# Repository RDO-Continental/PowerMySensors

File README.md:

# PowerMySensors
Code de notre module de mesure de puissance (Arduino + NRF + MySensors)

Mesure de puissance club RDO : MPRDO V1.0
 * Alimenté par un transfo qui sert aussi à la mesure de la puissance reelle.
 * Transmission par module NRF24L01 et protocole Mysensors
 * Basé sur le projet "openenergymonitor.org"

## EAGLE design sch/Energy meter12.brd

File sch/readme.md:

Schema de notre cartre de mesure

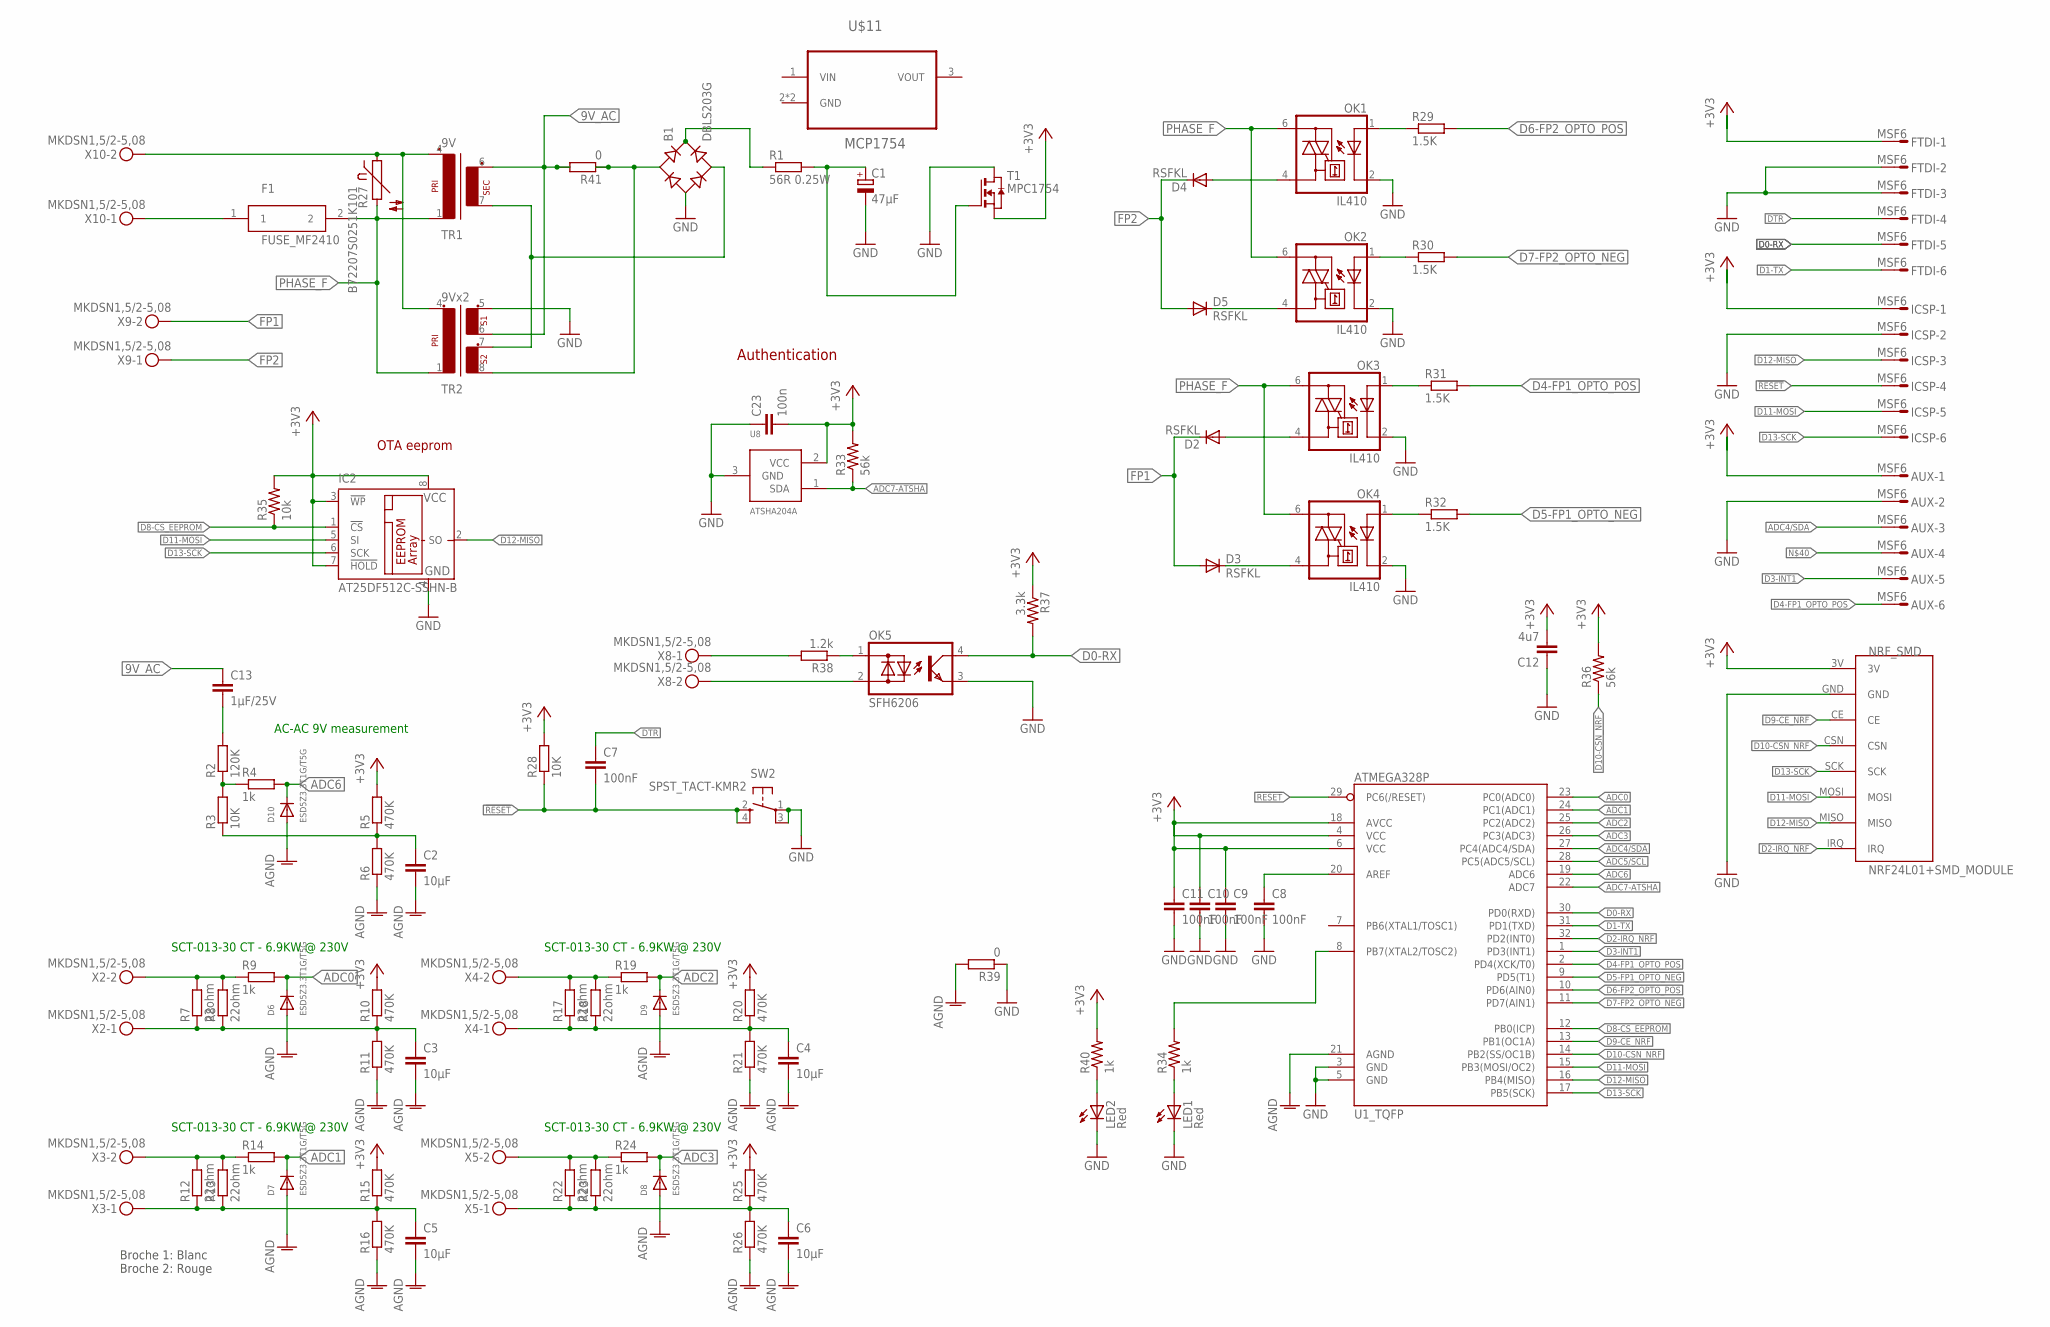
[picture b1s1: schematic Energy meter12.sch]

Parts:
AUX: MSF6
B1: DBLS203G; DBS
C1: 47µF; PANASONIC_D
C2, C3, C4, C5, C6: 10µF; C0805
C7, C8, C9, C10, C11: 100nF; C0603
C12: 4u7; 0805-CAP
C13: 1µF/25V; C0805
C23: 100n; 0603-CAP
D2, D3, D4, D5: RSFKL; SOD123
D6, D7, D8, D9, D10: ESD5Z3.3T1G/T5G; SOD-523
F1: FUSE_MF2410; 2410
FTDI: MSF6
IC2: AT25DF512C-SSHN-B; SO-08
ICSP: MSF6
LED1, LED2: Red; LED3MM
NRF_SMD: NRF24L01+SMD_MODULE
OK1, OK2, OK3, OK4: IL410; DIL06
OK5: SFH6206; DIL4-SMD
R1: 56R 0.25W; R1206
R2: 120K; R0603
R3, R28: 10K; R0603
R4, R9, R14, R19, R24: 1k; R0603
R5, R6, R10, R11, R15, R16, R20, R21, R25, R26: 470K; R0603
R7, R12, R17, R22: 22ohm; R1206
R8, R13, R18, R23: 22ohm; 0204/7
R27: B72207S0251K101; 07S0251
R29, R30, R31, R32: 1.5K; R0603
R33: 56k; 0603-RES
R34, R40: 1k; 0805-RES
R35: 10k; 0805-RES
R36: 56k; 0805-RES
R37: 3.3k; 0603-RES
R38: 1.2k; 0204/7
R39, R41: 0; R0603
SW2: SPST_TACT-KMR2; KMR2
T1: MPC1754; SOT89
TR1: 9V; PT150901
TR2: 9Vx2; EE20-2
U1_TQFP: ATMEGA328P; TQFP32-08
U8: ATSHA204A; SOT23
U$11: MCP1754; SOT89
X2, X3, X4, X5, X8, X9, X10: MKDSN1,5/2-5,08

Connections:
9V_AC: C13.1, R41.2, TR1.6 (S3), TR2.6 (4)
!RESET: C7.2, ICSP.4, R28.1, SW2.2 (S), SW2.4 (S1), U1_TQFP.29 (PC6(/RESET))
+3V3: AUX.1, C9.1, C10.1, C11.1, C12.2, C23.2, FTDI.1, IC2.3 (!WP), IC2.7 (!HOLD), IC2.8 (VCC), ICSP.1, NRF_SMD.3V, R5.2, R10.2, R15.2, R20.2, R25.2, R28.2, R33.2, R35.2, R36.2, R37.1, R40.2, T1.3 (S), U1_TQFP.4 (VCC), U1_TQFP.6 (VCC), U1_TQFP.18 (AVCC), U8.2 (VCC)
ADC0: D6.K (C), R9.2, U1_TQFP.23 (PC0(ADC0))
ADC1: D7.K (C), R14.2, U1_TQFP.24 (PC1(ADC1))
ADC2: D9.K (C), R19.2, U1_TQFP.25 (PC2(ADC2))
ADC3: D8.K (C), R24.2, U1_TQFP.26 (PC3(ADC3))
ADC4/SDA: AUX.3, U1_TQFP.27 (PC4(ADC4/SDA))
ADC5/SCL: U1_TQFP.28 (PC5(ADC5/SCL))
ADC6: D10.K (C), R4.2, U1_TQFP.19 (ADC6)
ADC7-ATSHA: R33.1, U1_TQFP.22 (ADC7), U8.1 (SDA)
AGND: C2.2, C3.2, C4.2, C5.2, C6.2, D6.A, D7.A, D8.A, D9.A, D10.A, R6.1, R11.1, R16.1, R21.1, R26.1, R39.2, U1_TQFP.21 (AGND)
D0-RX: FTDI.5, OK5.4 (C), R37.2, U1_TQFP.30 (PD0(RXD))
D1-TX: FTDI.6, U1_TQFP.31 (PD1(TXD))
D2-IRQ_NRF: NRF_SMD.IRQ, U1_TQFP.32 (PD2(INT0))
D3-INT1: AUX.5, U1_TQFP.1 (PD3(INT1))
D4-FP1_OPTO_POS: AUX.6, R31.2, U1_TQFP.2 (PD4(XCK/T0))
D5-FP1_OPTO_NEG: R32.2, U1_TQFP.9 (PD5(T1))
D6-FP2_OPTO_POS: R29.2, U1_TQFP.10 (PD6(AIN0))
D7-FP2_OPTO_NEG: R30.2, U1_TQFP.11 (PD7(AIN1))
D8-CS_EEPROM: IC2.1 (!CS), R35.1, U1_TQFP.12 (PB0(ICP))
D9-CE_NRF: NRF_SMD.CE, U1_TQFP.13 (PB1(OC1A))
D10-CSN_NRF: NRF_SMD.CSN, R36.1, U1_TQFP.14 (PB2(SS/OC1B))
D11-MOSI: IC2.5 (SI), ICSP.5, NRF_SMD.MOSI, U1_TQFP.15 (PB3(MOSI/OC2))
D12-MISO: IC2.2 (SO), ICSP.3, NRF_SMD.MISO, U1_TQFP.16 (PB4(MISO))
D13-SCK: IC2.6 (SCK), ICSP.6, NRF_SMD.SCK, U1_TQFP.17 (PB5(SCK))
DTR: C7.1, FTDI.4
FP1: D2.C, D3.A, X9.2
FP2: D4.C, D5.A, X9.1
GND: AUX.2, B1.-, C1.-, C8.2, C9.2, C10.2, C11.2, C12.1, C23.1, FTDI.2, FTDI.3, IC2.4 (GND), ICSP.2, LED1.K (C), LED2.K (C), NRF_SMD.GND, OK1.2 (C), OK2.2 (C), OK3.2 (C), OK4.2 (C), OK5.3 (E), R39.1, SW2.1, SW2.3 (P1), T1.2 (D), T1.2@1 (D), TR2.5 (3), U1_TQFP.3 (GND), U1_TQFP.5 (GND), U8.3 (GND)
unnamed: B1.AC1, R41.1, TR2.8 (6)
unnamed: C1.+, R1.2, T1.1 (G)
unnamed: R2.1, R3.2, R4.1
unnamed: C2.1, R3.1, R5.1, R6.2
unnamed: D4.A, OK1.4 (A1)
unnamed: R7.2, R8.2, R9.1, X2.2
unnamed: C3.1, R7.1, R8.1, R10.1, R11.2, X2.1
unnamed: LED2.A, R40.1
unnamed: R12.2, R13.2, R14.1, X3.2
unnamed: C5.1, R12.1, R13.1, R15.1, R16.2, X3.1
unnamed: R17.2, R18.2, R19.1, X4.2
unnamed: C4.1, R17.1, R18.1, R20.1, R21.2, X4.1
unnamed: R22.2, R23.2, R24.1, X5.2
unnamed: C6.1, R22.1, R23.1, R25.1, R26.2, X5.1
unnamed: C8.1, U1_TQFP.20 (AREF)
unnamed: D2.A, OK3.4 (A1)
unnamed: D5.C, OK2.4 (A1)
unnamed: OK1.1 (A), R29.1
unnamed: OK2.1 (A), R30.1
unnamed: R38.2, X8.1
unnamed: D3.C, OK4.4 (A1)
unnamed: OK3.1 (A), R31.1
unnamed: OK4.1 (A), R32.1
unnamed: OK5.1 (AC1), R38.1
unnamed: OK5.2 (AC2), X8.2
unnamed: B1.+, R1.1
unnamed: C13.2, R2.2
unnamed: LED1.A, R34.1
unnamed: R34.2, U1_TQFP.8 (PB7(XTAL2/TOSC2))
unnamed: R27.1, TR1.4 (P2), TR2.4 (2), X10.2
unnamed: B1.AC2, TR1.7 (S4), TR2.7 (5)
unnamed: F1.1, X10.1
PHASE_F: F1.2, OK1.6 (A2), OK2.6 (A2), OK3.6 (A2), OK4.6 (A2), R27.2, TR1.1, TR2.1

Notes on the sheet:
AC-AC 9V measurement
SCT-013-30 CT - 6.9KW @ 230V
Broche 1: Blanc Broche 2: Rouge
Authentication
OTA eeprom

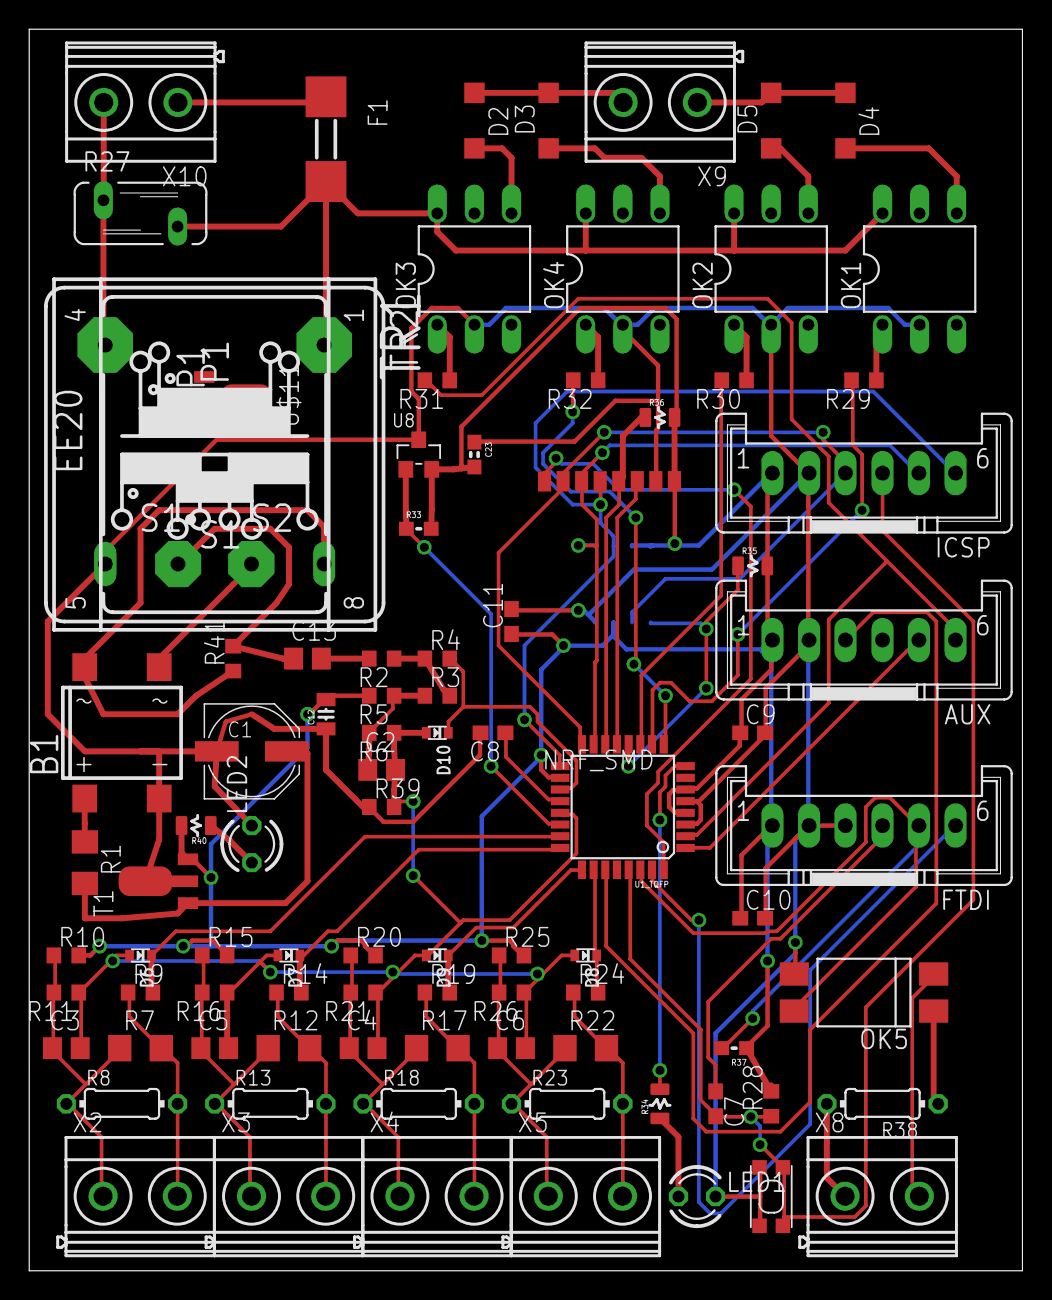
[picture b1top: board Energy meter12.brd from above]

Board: 2 copper layers, 68.0 x 85.0 mm, 92 parts (1 on the bottom side), 62 nets.

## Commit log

2021-11-09 Rename PowerMysensor.ino to src/PowerMysensor.ino

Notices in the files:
parts and their libraries:
microbuilder: This work is placed in the public domain, and may be freely used for commercial and non-commercial work with the following conditions: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
SparkFun-DigitalIC: Licensing: CC v3.0 Share-Alike You are welcome to use this library for commercial purposes.
